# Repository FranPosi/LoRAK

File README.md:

# LoRAK

version 2.1 21-Feb-2024

-----------------------

Printed on both layer of low cost FR-4 (0.8 mm thick) substrate. 

Schematics, KiCad project files and Gerbers export .zip files are included in folder [CAD](https://github.com/FranPosi/LoRAK/tree/main/CAD).

A CST Studio Suite 2023 files are stored in [CST_models](https://github.com/FranPosi/LoRAK/tree/main/CST_models)

## Measurements: 

|S11| simulated and measured results comparison:

And measured RHCP and LHCP radiation pattern: 

-----------------------

all measured data and Python script to reproduce these plots are available in [Measurements_plots](https://github.com/FranPosi/LoRAK/tree/main/Measurements_plots)

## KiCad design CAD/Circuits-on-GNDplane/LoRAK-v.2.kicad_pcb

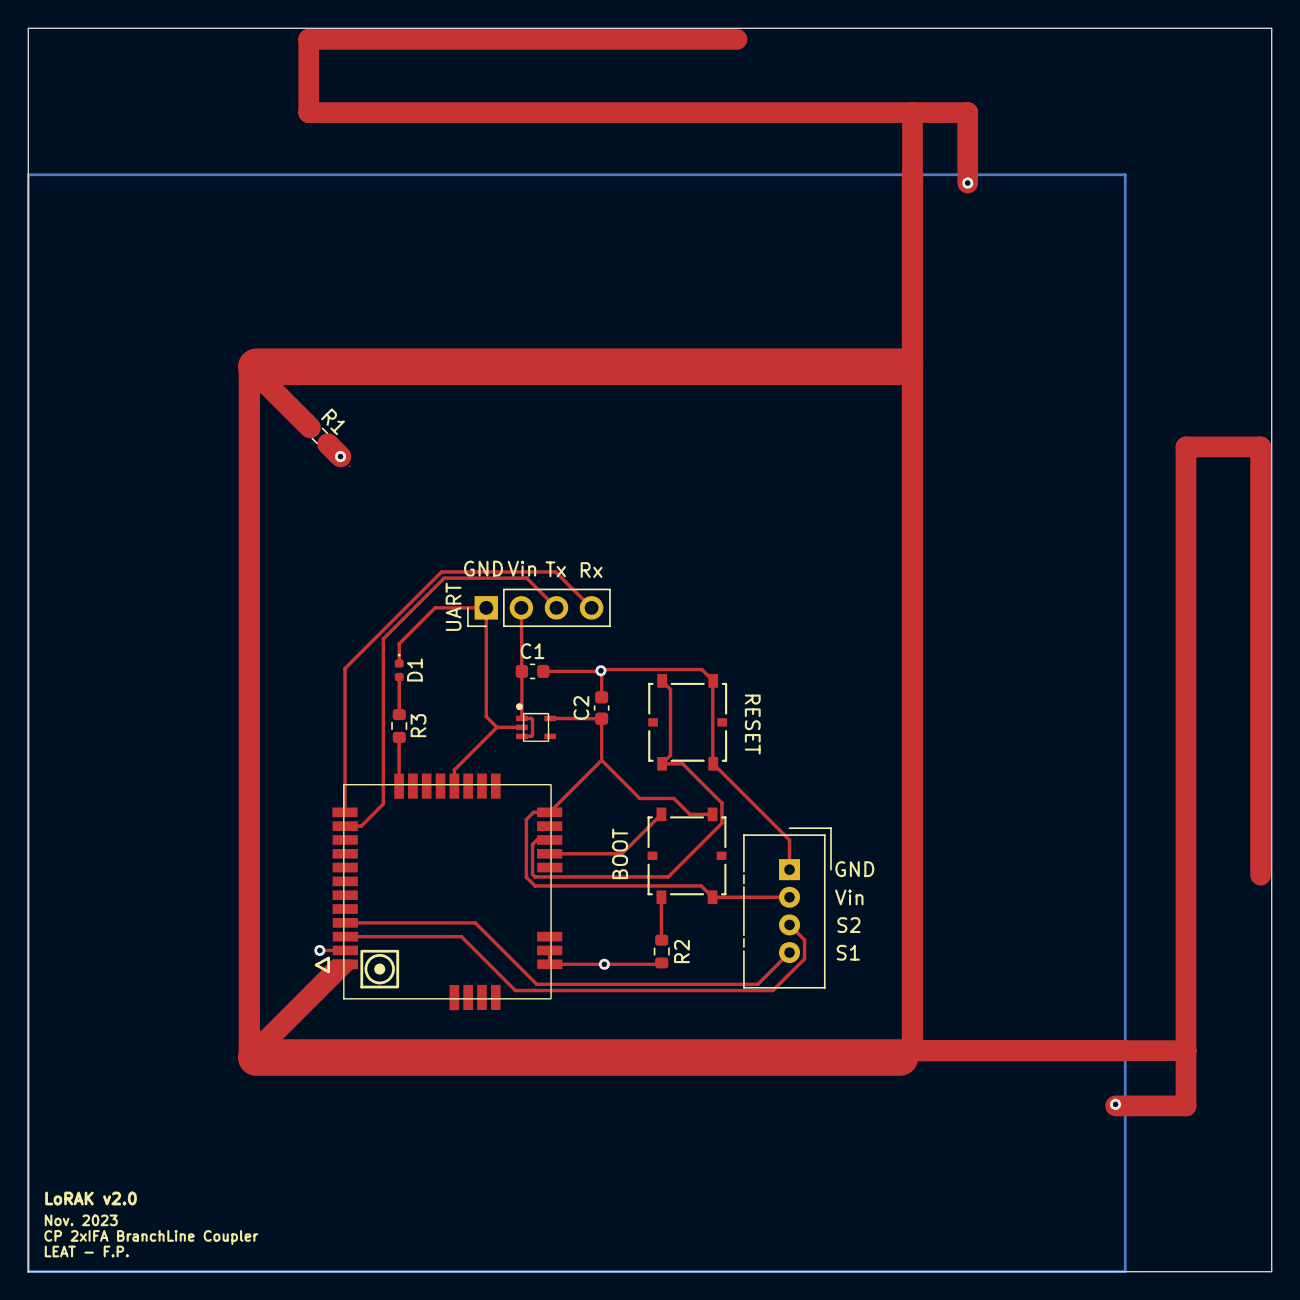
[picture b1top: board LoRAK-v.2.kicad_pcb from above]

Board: 2 copper layers, 90.0 x 90.0 mm, 12 parts (0 on the bottom side), 12 nets.

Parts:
C1, C2: 10uF; C_0603_1608Metric
D1: LED; LED_0402_1005Metric
J2: I2C; Grove_2.0
R1, R2, R3: R; R_0603_1608Metric
RAK3172(H)1: RAK3172
SW1, SW3: PTS526
U1: STLQ020
UART: UART; PinHeader_1x04_P2.54mm_Vertical

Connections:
+3.3V: C2.1, J2.2, RAK3172(H)1.24 (VDD), SW1.3, SW1.4, U1.5 (Vout)
/RF_OUT: R1.1, RAK3172(H)1.12 (RF)
/RX: RAK3172(H)1.1 (UART2_RX), UART.4
/S1: J2.4, RAK3172(H)1.9 (I2C_SCL)
/S2: J2.3, RAK3172(H)1.10 (I2C_SDA)
/TX: RAK3172(H)1.2 (UART2_TX), UART.3
/VIN: C1.1, U1.1 (Vin), U1.3 (EN), UART.2
GND: C1.2, C2.2, D1.1 (K), J2.1, R1.2, R2.2, RAK3172(H)1.11 (GND), RAK3172(H)1.17 (GND), RAK3172(H)1.18 (GND), RAK3172(H)1.28 (GND), SW3.3, SW3.4, U1.2 (GND), UART.1
unnamed: D1.2 (A), R3.1
unnamed: R3.2, RAK3172(H)1.32 (ADC1)
unnamed: R2.1, RAK3172(H)1.21 (BOOT), SW1.1, SW1.2
unnamed: RAK3172(H)1.22 (RST), SW3.1, SW3.2

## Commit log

2024-02-21 update21Feb2024
2024-02-21 Measurements
2024-02-21 last readme
